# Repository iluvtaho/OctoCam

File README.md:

# OctoCam
Half-Life Hackclub

OctoCam’s features:
Basic camera functions e.g. take photos and videos and store them to a microsd card.
Rechargeable battery

"Schematic Diagram"

"PCB Diagram"

"System Architecture"

Research DOC: https://docs.google.com/document/d/1c9nwyoibegYjvhpOvqnHpFpebzzNYjcU_NpFNvT4hUc/edit?usp=sharing

"3D Model of CAD"

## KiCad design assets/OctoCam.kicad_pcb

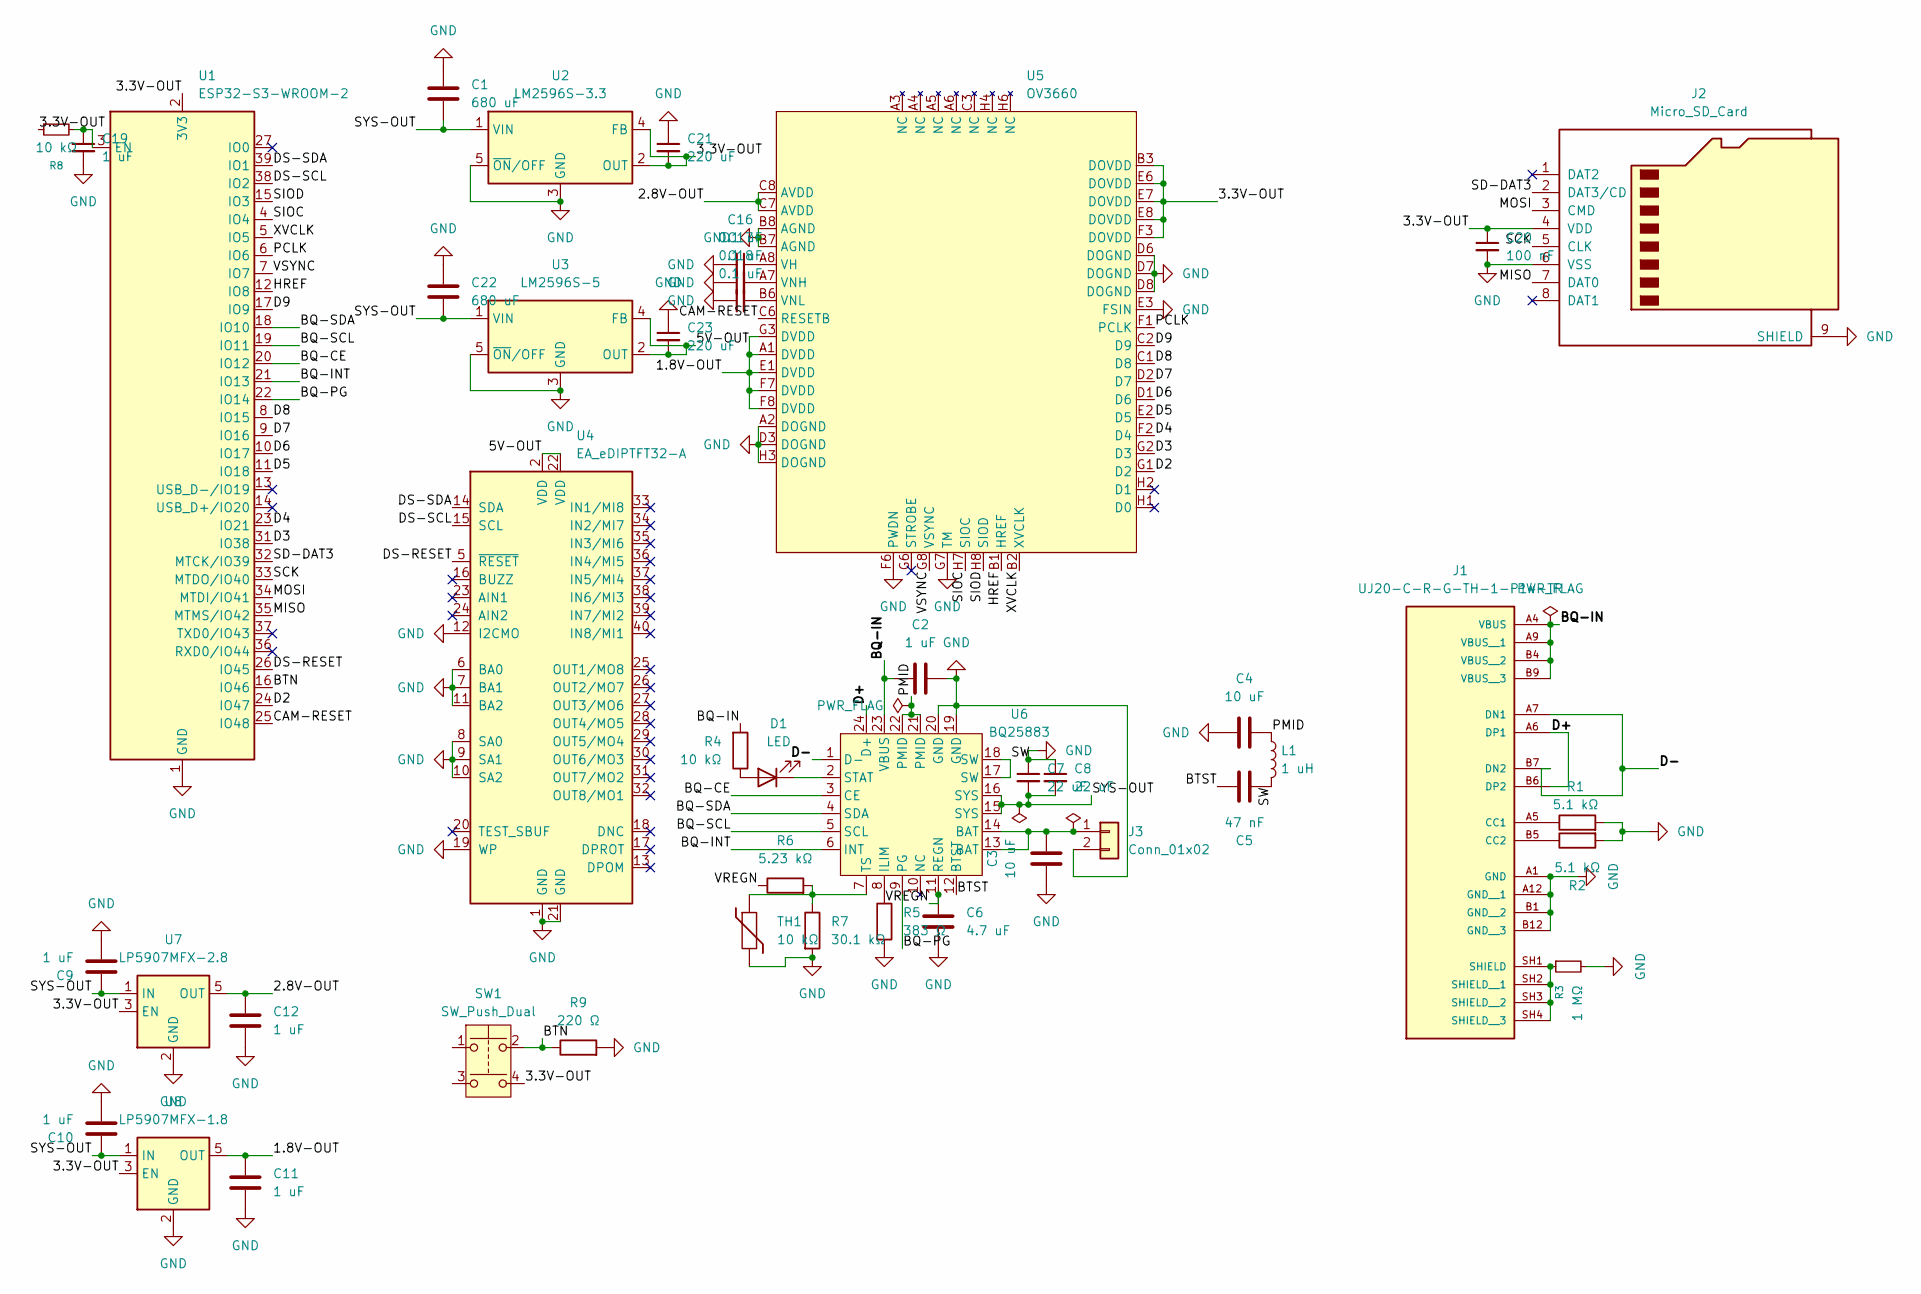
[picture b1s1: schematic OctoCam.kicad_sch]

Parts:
C1, C22: 680 uF; C_0201_0603Metric
C2, C9, C10, C11, C12, C19: 1 uF; C_0201_0603Metric
C3, C4: 10 uF; C_0201_0603Metric
C5: 47 nF; C_0201_0603Metric
C6: 4.7 uF; C_0201_0603Metric
C7, C8: 22 uF; C_0201_0603Metric
C16, C17, C18: 0.1 uF; C_0201_0603Metric
C20: 100 nF; C_0201_0603Metric
C21, C23: 220 uF; C_0201_0603Metric
D1: LED; LED_Rectangular_W3.0mm_H2.0mm
J1: UJ20-C-R-G-TH-1-P14-TR; SAMESKY_UJ20-C-R-G-TH-1-P14-TR; PARTREV 1.0
J2: Micro_SD_Card; microSD_HC_Molex_47219-2001
J3: Conn_01x02; PinHeader_1x02_P1.00mm_Vertical
L1: 1 uH; L_APV_ANR3010
R1, R2: 5.1 kΩ; R_0201_0603Metric
R3: 1 MΩ; R_0201_0603Metric
R4, R8: 10 kΩ; R_0201_0603Metric
R5: 383 Ω; R_0201_0603Metric
R6: 5.23 kΩ; R_0201_0603Metric
R7: 30.1 kΩ; R_0201_0603Metric
R9: 220 Ω; R_0201_0603Metric
SW1: SW_Push_Dual; SW_Push_2P1T_Toggle_CK_PVA1xxH1xxxxxxV2
TH1: 10 kΩ; R_0201_0603Metric
U1: ESP32-S3-WROOM-2
U2: LM2596S-3.3; TO-263-5_TabPin3
U3: LM2596S-5; TO-263-5_TabPin3
U4: EA_eDIPTFT32-A; EA_eDIPTFT32-XXX
U5: OV3660
U6: BQ25883; VQFN24_RGE_TEX
U7: LP5907MFX-2.8; SOT-23-5
U8: LP5907MFX-1.8; SOT-23-5

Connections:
/1.8V-OUT: C11.1, U5.A1 (DVDD), U5.E1 (DVDD), U5.F7 (DVDD), U5.F8 (DVDD), U5.G3 (DVDD), U8.5 (OUT)
/2.8V-OUT: C12.1, U5.C7 (AVDD), U5.C8 (AVDD), U7.5 (OUT)
/3.3V-OUT: C20.1, C21.2, J2.4 (VDD), R8.1, SW1.4, U1.2 (3V3), U2.2 (OUT), U2.4 (FB), U5.B3 (DOVDD), U5.E6 (DOVDD), U5.E7 (DOVDD), U5.E8 (DOVDD), U5.F3 (DOVDD), U7.3 (EN), U8.3 (EN)
/5V-OUT: C23.2, U3.2 (OUT), U3.4 (FB), U4.2 (VDD), U4.22 (VDD)
/BQ-CE: U1.20 (IO12), U6.3 (CE)
/BQ-IN: C2.2, J1.A4 (VBUS), J1.A9 (VBUS__1), J1.B4 (VBUS__2), J1.B9 (VBUS__3), R4.2, U6.23 (VBUS)
/BQ-INT: U1.21 (IO13), U6.6 (INT)
/BQ-PG: U1.22 (IO14), U6.9 (PG)
/BQ-SCL: U1.19 (IO11), U6.5 (SCL)
/BQ-SDA: U1.18 (IO10), U6.4 (SDA)
/BTN: R9.1, SW1.2, U1.16 (IO46)
/BTST: C5.1, U6.12 (BTST)
/CAM-RESET: U1.25 (IO48), U5.C6 (RESETB)
/D2: U1.24 (IO47), U5.G1 (D2)
/D3: U1.31 (IO38), U5.G2 (D3)
/D4: U1.23 (IO21), U5.F2 (D4)
/D5: U1.11 (IO18), U5.E2 (D5)
/D6: U1.10 (IO17), U5.D1 (D6)
/D7: U1.9 (IO16), U5.D2 (D7)
/D8: U1.8 (IO15), U5.C1 (D8)
/D9: U1.17 (IO9), U5.C2 (D9)
/D+: J1.A6 (DP1), J1.B6 (DP2), U6.24 (D+)
/D-: J1.A7 (DN1), J1.B7 (DN2), U6.1 (D-)
/DS-RESET: U1.26 (IO45), U4.5 (~RESET)
/DS-SCL: U1.38 (IO2), U4.15 (SCL)
/DS-SDA: U1.39 (IO1), U4.14 (SDA)
/HREF: U1.12 (IO8), U5.B1 (HREF)
/MISO: J2.7 (DAT0), U1.35 (MTMS/IO42)
/MOSI: J2.3 (CMD), U1.34 (MTDI/IO41)
/PCLK: U1.6 (IO6), U5.F1 (PCLK)
/PMID: C4.2, L1.1, U6.21 (PMID), U6.22 (PMID)
/SCK: J2.5 (CLK), U1.33 (MTDO/IO40)
/SD-DAT3: J2.2 (DAT3/CD), U1.32 (MTCK/IO39)
/SIOC: U1.4 (IO4), U5.H7 (SIOC)
/SIOD: U1.15 (IO3), U5.H8 (SIOD)
/SW: C5.2, L1.2, U6.17 (SW), U6.18 (SW)
/SYS-OUT: C1.2, C7.2, C8.2, C9.1, C10.1, C22.2, U2.1 (VIN), U3.1 (VIN), U6.15 (SYS), U6.16 (SYS), U7.1 (IN), U8.1 (IN)
/VREGN: C6.1, R6.1, U6.11 (REGN)
/VSYNC: U1.7 (IO7), U5.G8 (VSYNC)
/XVCLK: U1.5 (IO5), U5.B2 (XVCLK)
GND: C1.1, C2.1, C3.1, C4.1, C6.2, C7.1, C8.1, C9.2, C10.2, C11.2, C12.2, C16.2, C17.1, C18.1, C19.2, C20.2, C21.1, C22.1, C23.1, J1.A1 (GND), J1.A12 (GND__1), J1.B1 (GND__2), J1.B12 (GND__3), J2.6 (VSS), J2.9 (SHIELD), J3.2, R1.2, R2.2, R3.2, R5.2, R7.2, R9.2, TH1.2, U1.1 (GND), U1.40 (GND), U1.41 (GND), U2.3 (GND), U2.5 (~ON/OFF), U3.3 (GND), U3.5 (~ON/OFF), U4.1 (GND), U4.6 (BA0), U4.7 (BA1), U4.8 (SA0), U4.9 (SA1), U4.10 (SA2), U4.11 (BA2), U4.12 (I2CMO), U4.19 (WP), U4.21 (GND), U5.A2 (DOGND), U5.B7 (AGND), U5.B8 (AGND), U5.D3 (DOGND), U5.D6 (DOGND), U5.D7 (DOGND), U5.D8 (DOGND), U5.E3 (FSIN), U5.F6 (PWDN), U5.G7 (TM), U5.H3 (DOGND), U6.19 (GND), U6.20 (GND), U7.2 (GND), U8.2 (GND)
unnamed: D1.2 (A), R4.1
unnamed: D1.1 (K), U6.2 (STAT)
unnamed: J1.A5 (CC1), R1.1
unnamed: J1.B5 (CC2), R2.1
unnamed: J1.SH1 (SHIELD), J1.SH2 (SHIELD__1), J1.SH3 (SHIELD__2), J1.SH4 (SHIELD__3), R3.1
unnamed: C3.2, J3.1, U6.13 (BAT), U6.14 (BAT)
unnamed: C19.1, R8.2, U1.3 (EN)
unnamed: C16.1, U5.A8 (VH)
unnamed: C17.2, U5.A7 (VNH)
unnamed: C18.2, U5.B6 (VNL)
unnamed: R5.1, U6.8 (ILIM)
unnamed: R6.2, R7.1, TH1.1, U6.7 (TS)

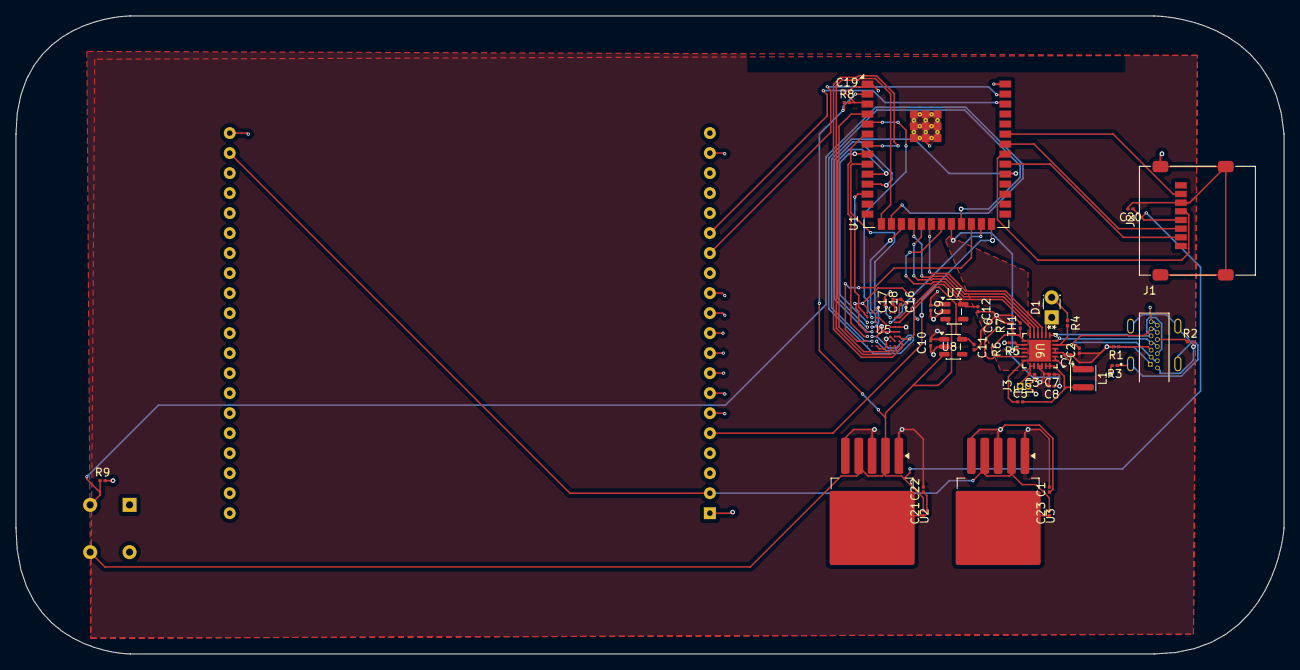
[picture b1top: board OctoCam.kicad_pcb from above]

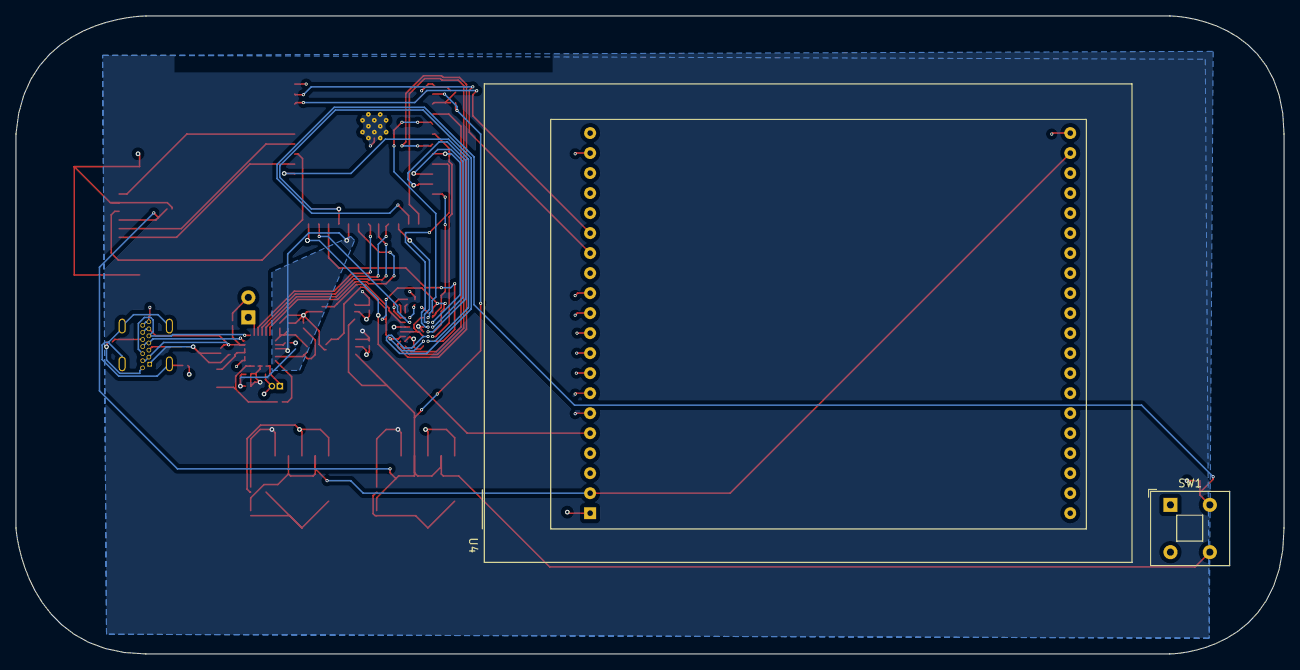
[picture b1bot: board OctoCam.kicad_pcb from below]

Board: 2 copper layers, 161.0 x 81.0 mm, 44 parts (2 on the bottom side), 53 nets.
